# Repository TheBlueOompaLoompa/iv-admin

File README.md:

# Prototype Microgravity IV Administartion System

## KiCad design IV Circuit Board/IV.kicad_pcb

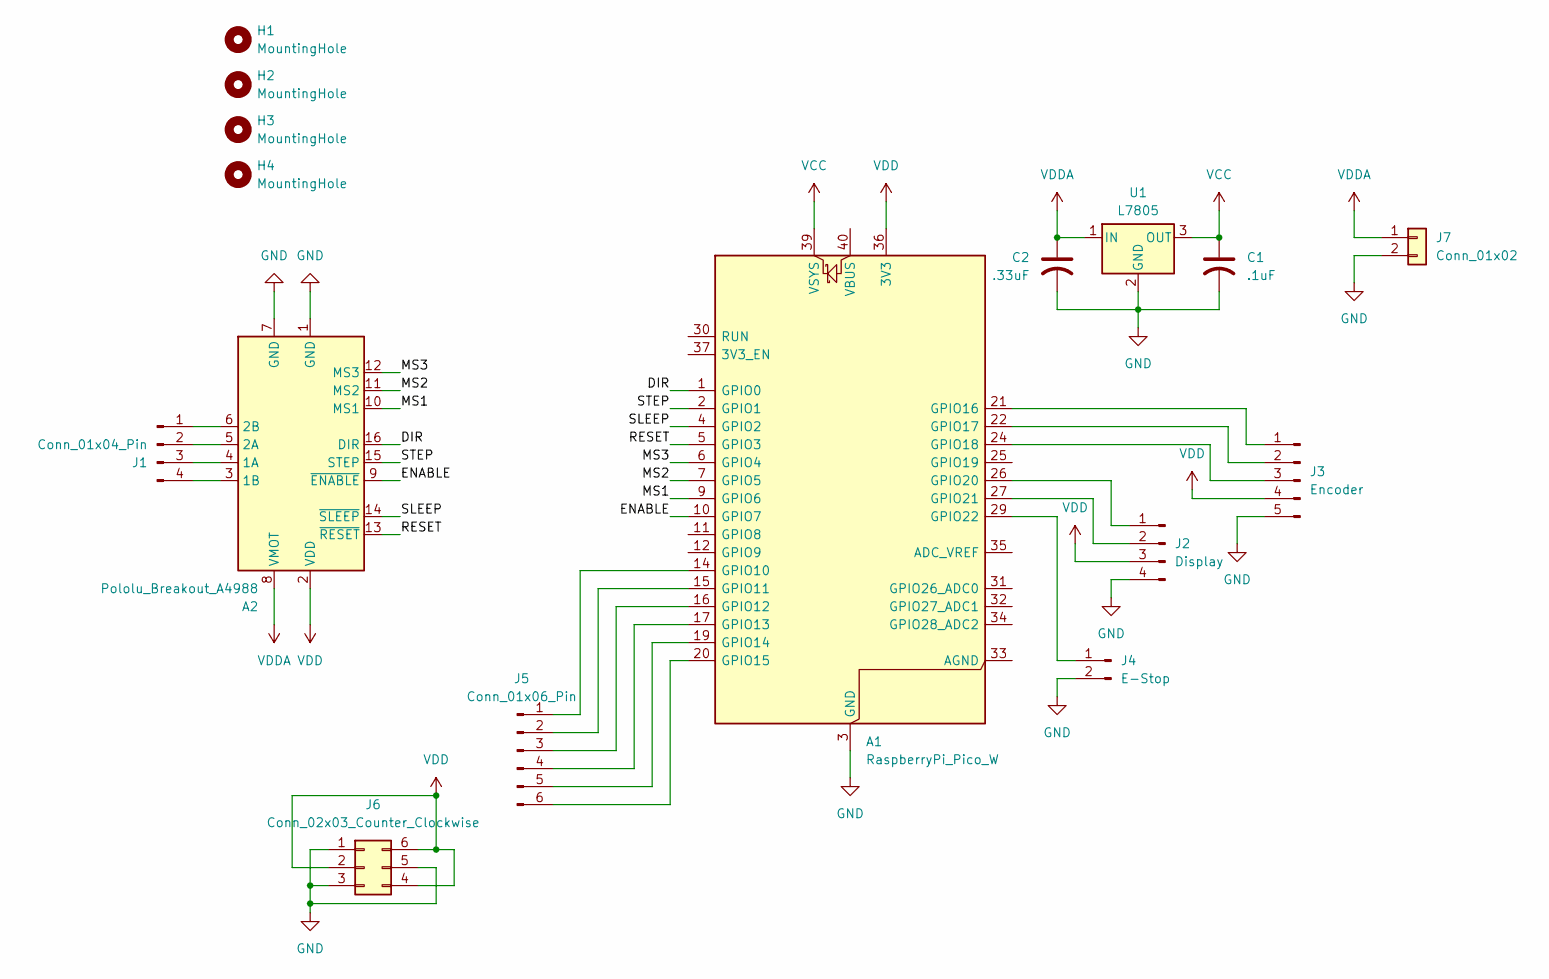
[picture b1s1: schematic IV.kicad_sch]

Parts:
A1: RaspberryPi_Pico_W; RaspberryPi_Pico_Common_THT
A2: Pololu_Breakout_A4988; Pololu_Breakout-16_15.2x20.3mm
C1: .1uF; C_Radial_D6.3mm_H7.0mm_P2.50mm
C2: .33uF; C_Radial_D6.3mm_H7.0mm_P2.50mm
H1, H2, H3, H4: MountingHole; MountingHole_2.2mm_M2
J1: Conn_01x04_Pin; PinHeader_1x04_P2.54mm_Vertical
J2: Display; PinHeader_1x04_P2.54mm_Vertical
J3: Encoder; PinHeader_1x05_P2.54mm_Vertical
J4: E-Stop; PinHeader_1x02_P2.54mm_Vertical
J5: Conn_01x06_Pin; PinHeader_1x06_P2.54mm_Vertical
J6: Conn_02x03_Counter_Clockwise; PinHeader_2x03_P2.54mm_Vertical
J7: Conn_01x02; JST_PH_B2B-PH-K_1x02_P2.00mm_Vertical
U1: L7805; TO-220F-3_Horizontal_TabDown

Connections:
/DIR: A1.1 (GPIO0), A2.16 (DIR)
/ENABLE: A1.10 (GPIO7), A2.9 (~ENABLE)
/MS1: A1.9 (GPIO6), A2.10 (MS1)
/MS2: A1.7 (GPIO5), A2.11 (MS2)
/MS3: A1.6 (GPIO4), A2.12 (MS3)
/RESET: A1.5 (GPIO3), A2.13 (~RESET)
/SLEEP: A1.4 (GPIO2), A2.14 (~SLEEP)
/STEP: A1.2 (GPIO1), A2.15 (STEP)
GND: A1.3 (GND), A1.8 (GND), A1.13 (GND), A1.18 (GND), A1.23 (GND), A1.28 (GND), A1.38 (GND), A2.1 (GND), A2.7 (GND), C1.2, C2.2, J2.4, J3.5, J4.2, J6.1, J6.3, J6.5, J7.2, U1.2 (GND)
unnamed: A1.14 (GPIO10), J5.1
unnamed: A1.15 (GPIO11), J5.2
unnamed: A1.16 (GPIO12), J5.3
unnamed: A1.17 (GPIO13), J5.4
unnamed: A1.19 (GPIO14), J5.5
unnamed: A1.20 (GPIO15), J5.6
unnamed: A1.21 (GPIO16), J3.1
unnamed: A1.22 (GPIO17), J3.2
unnamed: A1.24 (GPIO18), J3.3
unnamed: A1.26 (GPIO20), J2.1
unnamed: A1.27 (GPIO21), J2.2
unnamed: A1.29 (GPIO22), J4.1
unnamed: A2.4 (1A), J1.3
unnamed: A2.3 (1B), J1.4
unnamed: A2.5 (2A), J1.2
unnamed: A2.6 (2B), J1.1
VCC: A1.39 (VSYS), C1.1, U1.3 (OUT)
VDD: A1.36 (3V3), A2.2 (VDD), J2.3, J3.4, J6.2, J6.4, J6.6
VDDA: A2.8 (VMOT), C2.1, J7.1, U1.1 (IN)

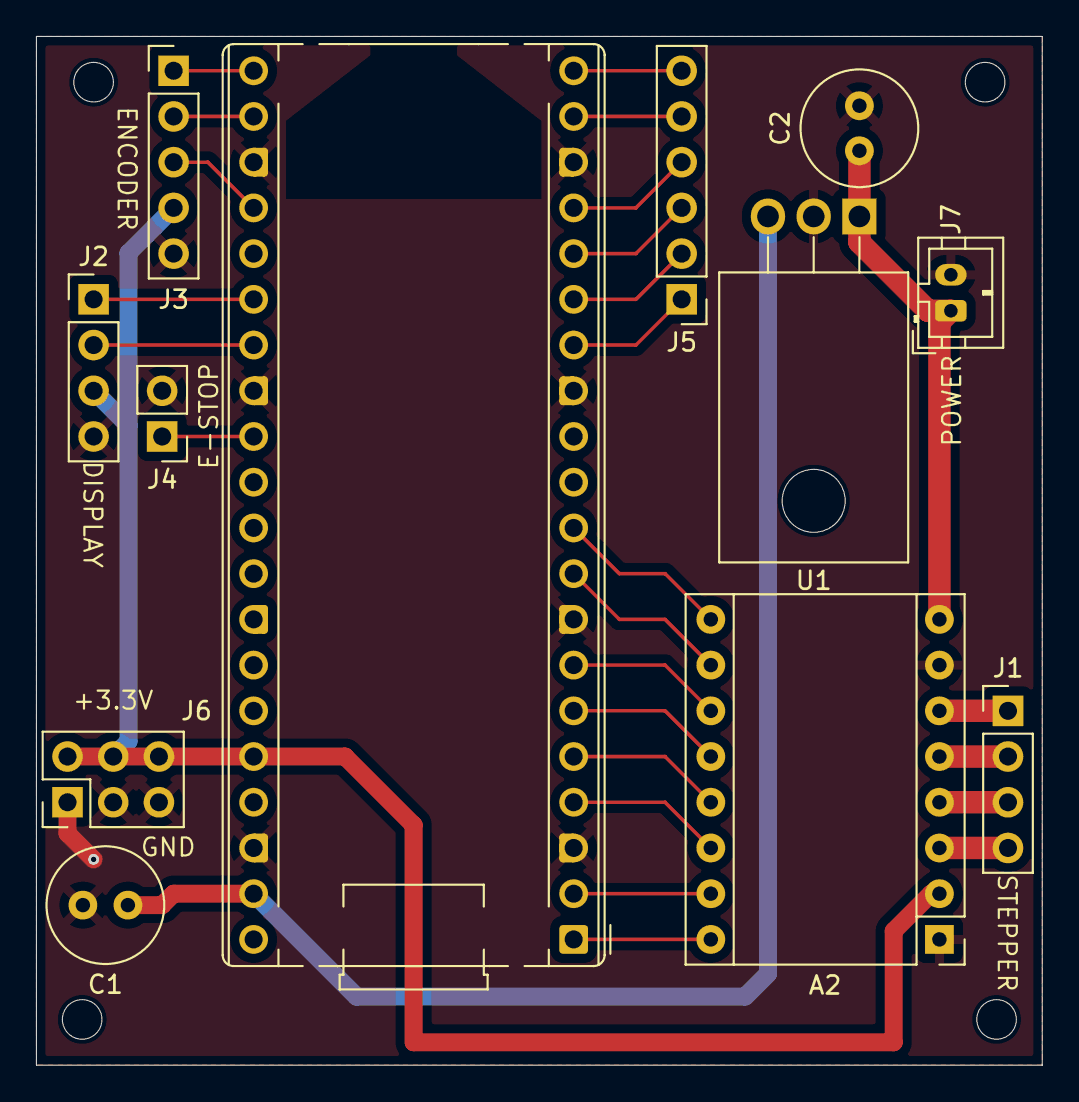
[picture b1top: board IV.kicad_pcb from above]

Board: 2 copper layers, 55.9 x 57.2 mm, 16 parts (0 on the bottom side), 28 nets.

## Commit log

2025-04-09 Put online
2025-05-28 Add circuit board
2025-05-28 Update gitignore
2025-05-28 Remove backups from repo
2026-05-29 Working version with updated packages
